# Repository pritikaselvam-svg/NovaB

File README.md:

# 🎧 NovaBuds

### An end-to-end headphone concept combining industrial design, ergonomics, embedded electronics and custom PCB development.

---

## What if I could take a pair of headphones from a concept sketch all the way to the electronics?

NovaBuds started with that question.

What began as a headphone design exercise turned into an exploration of what happens when **industrial design and electrical engineering are developed together**.

I designed the headphone form and ergonomics, developed the earcup and headband in CAD, designed the electronics architecture, built the schematic in KiCad, created a custom-shaped PCB around the product geometry, planned the embedded system and designed the ambient display interface.

The goal was not just to make a headphone that looked interesting.

It was to understand what it takes to make the **product, electronics and interaction work as one system.**

---

# ✦ Project Snapshot

| | |
|---|---|
| **Project** | NovaBuds |
| **Type** | Headphone / Wearable Electronics |
| **Focus** | Industrial Design × Embedded Systems |
| **CAD** | Onshape |
| **PCB Design** | KiCad |
| **MCU** | ESP32-S3-WROOM |
| **Charging** | BQ24074 |
| **Regulation** | AP2112K 3.3 V |
| **Audio** | I²S + MAX98357A |
| **Sensing** | Hall-effect sensor |
| **Interface** | TFT ambient display + physical buttons |
| **PCB** | Custom-shaped |
| **Status** | Engineering prototype in development |

---

# 01 — The Idea

Most headphone projects begin with either the industrial design or the electronics.

I wanted to explore both at the same time.

The starting point was a wearable form that could accommodate:

- a custom earcup geometry
- a headband structure
- a local display
- physical controls
- a battery
- audio electronics
- a wireless MCU
- a custom PCB

That immediately created an interesting constraint:

> **The electronics couldn't simply be designed first and placed inside a box afterwards.**

The product geometry had to influence the electronics.

And the electronics had to influence the product geometry.

---

# 02 — Product Direction

NovaBuds is designed around three ideas:

### 01. Product form

A distinctive earcup geometry developed around the human-facing side of the product rather than around a conventional rectangular electronics package.

### 02. Ambient interaction

A small display provides glanceable information such as playback state, battery and connectivity without requiring the user to constantly reach for a phone.

### 03. Integrated engineering

The mechanical enclosure, PCB and interaction system are treated as parts of the same product rather than independent projects.

---

# 03 — From Sketch to CAD

The first iterations were developed through physical sketches and form exploration.

The form was then developed in Onshape into the final earcup and headband geometry.

### CAD development

The CAD work focused on:

- earcup geometry
- headband structure
- component packaging
- display placement
- button placement
- internal volume
- PCB integration
- enclosure transitions

The final assembly was developed as a complete headphone rather than as isolated parts.

---

# 04 — Ergonomics

Because the product is worn directly on the head, the geometry had to be considered from the user's perspective.

The main ergonomic considerations were:

- ear clearance
- contact surfaces
- enclosure thickness
- edge transitions
- button reach
- display visibility
- headband geometry
- internal component clearance

The controls were positioned on the earcup so that common interactions could be performed without relying entirely on a phone.

The display was treated as an **ambient information surface** rather than a miniature smartphone screen.

> The current geometry is a design exploration. Formal anthropometric studies and physical user testing are planned for future iterations.

---

# 05 — Electronics Architecture

The electronics were designed around an ESP32-S3 as the central controller.

```text
                         ┌────────────────────┐
                         │      ESP32-S3      │
                         │   MCU + Wireless   │
                         └─────────┬──────────┘
                                   │
              ┌────────────────────┼────────────────────┐
              │                    │                    │
              ▼                    ▼                    ▼
         TFT Display           Buttons             Hall Sensor
              │
              │
              └─────────────────────┐
                                    │
                                    ▼
ESP32-S3 ─────── I²S ───────► MAX98357A ───────► Speaker

USB-C ───────► BQ24074 ───────► Li-ion Battery
                    │
                    ▼
                 AP2112K
                    │
                   3V3
                    │
                    └──────► Digital Electronics

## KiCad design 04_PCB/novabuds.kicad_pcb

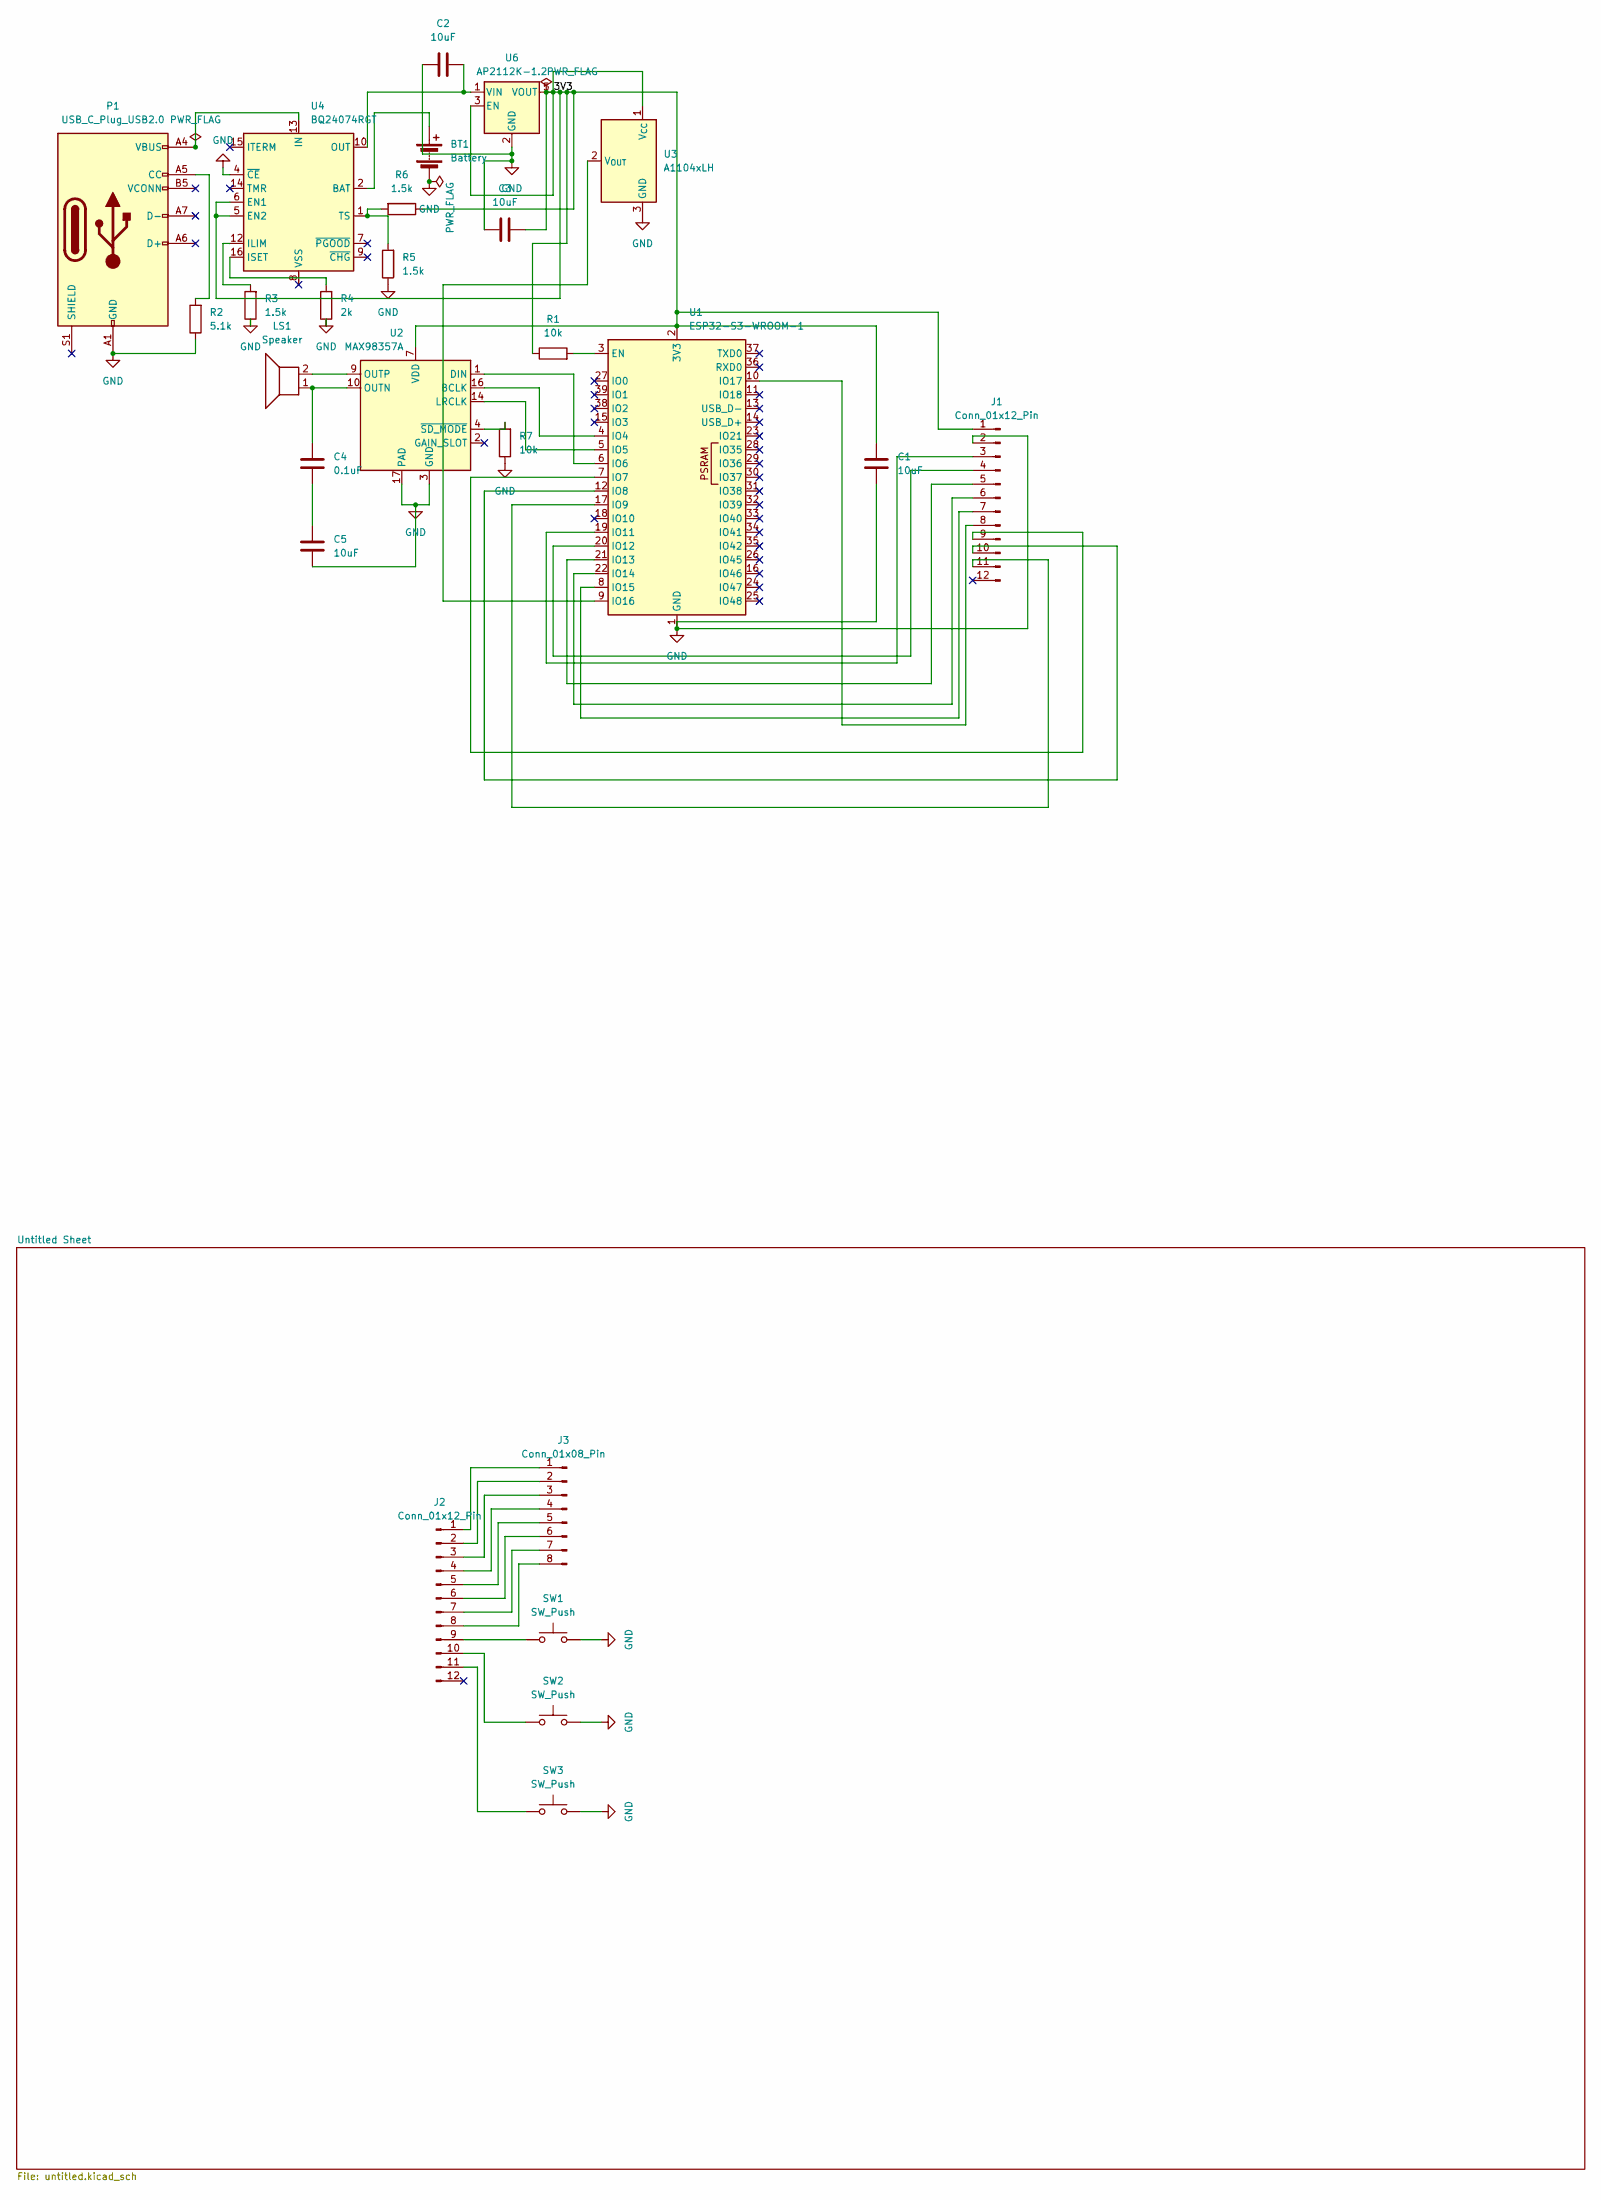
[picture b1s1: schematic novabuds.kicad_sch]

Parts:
BT1: Battery; JST_PH_B2B-PH-K_1x02_P2.00mm_Vertical
C1, C2, C3, C5: 10uF; C_0805_2012Metric
C4: 0.1uF; C_0805_2012Metric
J1, J2: Conn_01x12_Pin; PinHeader_1x12_P2.54mm_Vertical
J3: Conn_01x08_Pin; PinHeader_1x08_P2.54mm_Vertical
LS1: Speaker; PinHeader_1x02_P2.54mm_Vertical
P1: USB_C_Plug_USB2.0; USB_C_Receptacle_HRO_TYPE-C-31-M-12
R1, R7: 10k; R_0805_2012Metric
R2: 5.1k; R_0805_2012Metric
R3, R5, R6: 1.5k; R_0805_2012Metric
R4: 2k; R_0805_2012Metric
SW1, SW2, SW3: SW_Push; SW_PUSH_6mm
U1: ESP32-S3-WROOM-1
U2: MAX98357A; TQFN-16-1EP_3x3mm_P0.5mm_EP1.23x1.23mm
U3: A1104xLH; SOT-23W
U4: BQ24074RGT; VQFN-16-1EP_3x3mm_P0.5mm_EP1.6x1.6mm
U6: AP2112K-1.2; SOT-23-5

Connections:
/3V3: C1.1, C3.2, J1.1, R1.1, R6.1, U1.2 (3V3), U2.7 (VDD), U2.8 (VDD), U3.1 (V_{CC}), U4.5 (EN2), U4.6 (EN1), U6.3 (EN), U6.5 (VOUT)
GND: BT1.2 (-), C1.2, C2.1, C3.1, C5.2, J1.2, P1.A1 (GND), P1.A12 (GND), P1.B1 (GND), P1.B12 (GND), R2.1, R3.1, R4.1, R5.1, R7.1, SW1.2, SW2.2, SW3.2, U1.1 (GND), U1.40 (GND), U1.41 (GND), U2.3 (GND), U2.11 (GND), U2.15 (GND), U2.17 (PAD), U3.3 (GND), U4.4 (~CE), U6.2 (GND)
unnamed: BT1.1 (+), U4.2 (BAT), U4.3 (BAT)
unnamed: C4.2, C5.1
unnamed: J1.3, U1.19 (IO11)
unnamed: J1.4, U1.20 (IO12)
unnamed: J1.5, U1.21 (IO13)
unnamed: J1.6, U1.22 (IO14)
unnamed: J1.7, U1.8 (IO15)
unnamed: J1.8, U1.10 (IO17)
unnamed: J1.9, U1.7 (IO7)
unnamed: J1.10, U1.12 (IO8)
unnamed: J1.11, U1.17 (IO9)
unnamed: J2.1, J3.1
unnamed: J2.2, J3.2
unnamed: J2.3, J3.3
unnamed: J2.4, J3.4
unnamed: J2.5, J3.5
unnamed: J2.6, J3.6
unnamed: J2.7, J3.7
unnamed: J2.8, J3.8
unnamed: J2.9, SW1.1
unnamed: J2.10, SW2.1
unnamed: J2.11, SW3.1
unnamed: P1.A5 (CC), R2.2
unnamed: R1.2, U1.3 (EN)
unnamed: U1.4 (IO4), U2.16 (BCLK)
unnamed: U1.5 (IO5), U2.14 (LRCLK)
unnamed: U1.6 (IO6), U2.1 (DIN)
unnamed: U1.9 (IO16), U3.2 (V_{OUT})
unnamed: C4.1, LS1.1, U2.10 (OUTN)
unnamed: LS1.2, U2.9 (OUTP)
unnamed: R7.2, U2.4 (~SD_MODE)
unnamed: R3.2, U4.12 (ILIM)
unnamed: P1.A4 (VBUS), P1.A9 (VBUS), P1.B4 (VBUS), P1.B9 (VBUS), U4.13 (IN)
unnamed: R4.2, U4.16 (ISET)
unnamed: R5.2, R6.2, U4.1 (TS)
unnamed: C2.2, U4.10 (OUT), U4.11 (OUT), U6.1 (VIN)

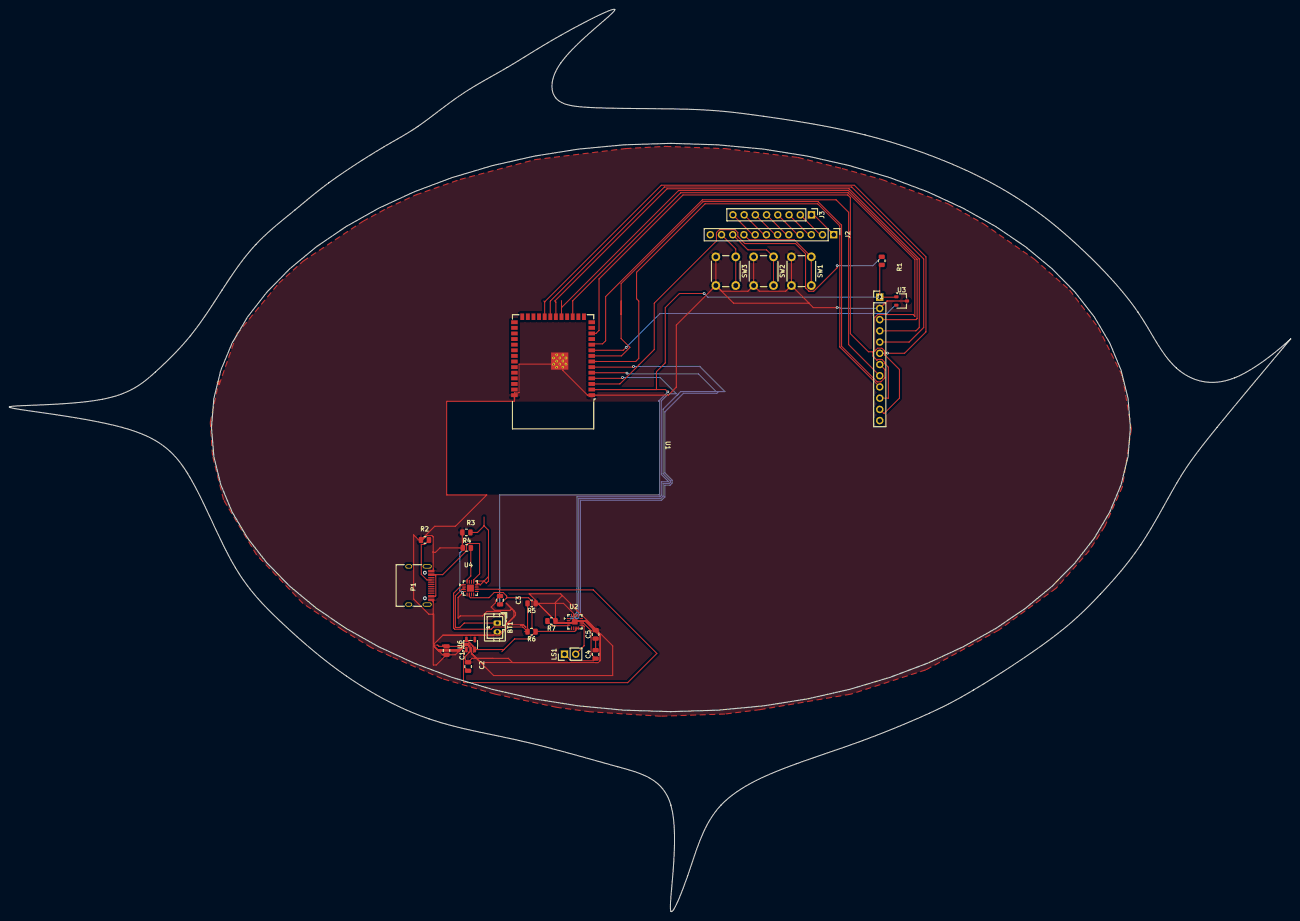
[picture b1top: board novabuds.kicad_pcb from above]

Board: 2 copper layers, 290.1 x 204.3 mm, 26 parts (0 on the bottom side), 38 nets.

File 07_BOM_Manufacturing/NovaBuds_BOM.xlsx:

Reference | Component | Function | Package / Footprint | Qty | Notes | Status
U1 | ESP32-S3-WROOM | MCU / wireless | RF module | 1 | Verify exact module pinout + antenna keepout | Designed
U2 | MAX98357A | I²S audio amplifier | Verify exact package | 1 | Verify supply and speaker requirements | Designed
U3 | A1104xLH | Hall sensor | SOT-23 | 1 | Verify exact variant | Designed
U4 | BQ24074 | Li-ion charger / power path | QFN | 1 | Verify ISET/ILIM/TS/EN1/EN2/CE | Designed
U6 | AP2112K-1.2 | 3.3 V LDO | SOT-23-5 | 1 | Verify exact ordering code | Designed
BT1 | 1-cell Li-ion battery | Energy storage | Battery connector/cell | 1 | Select protected cell/system | Concept
P1 | USB-C receptacle | Charging input | USB-C SMD | 1 | Verify exact footprint + CC network | Designed
LS1 | Speaker | Audio output | Mechanical part | 1 | Match amplifier requirements | Concept
J1 | 12-pin connector | Main interconnect | Verify selected footprint | 1 | Verify pinout | Designed
J2 | 12-pin connector | Interconnect | Verify selected footprint | 1 | Verify pinout | Designed
J3 | 8-pin connector | Display interface | 8-pin | 1 | Must match selected display | Designed
SW1 | Push button | User input | Verify selected footprint | 1 | GPIO | Designed
SW2 | Push button | User input | Verify selected footprint | 1 | GPIO | Designed
SW3 | Push button | User input | Verify selected footprint | 1 | GPIO | Designed
